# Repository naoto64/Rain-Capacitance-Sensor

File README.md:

# Rain-Capacitance-Sensor
This is the detection board for the capacitive rain sensor.

## Circuit board image

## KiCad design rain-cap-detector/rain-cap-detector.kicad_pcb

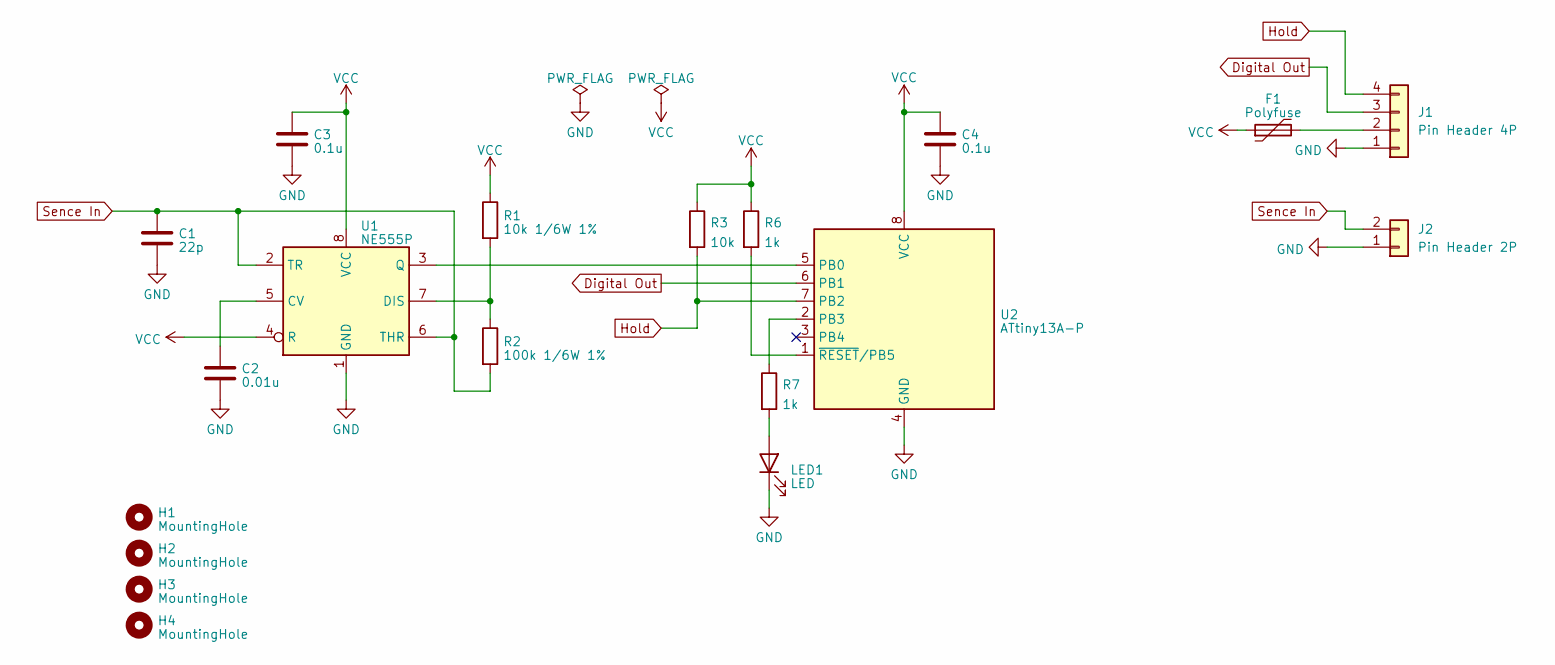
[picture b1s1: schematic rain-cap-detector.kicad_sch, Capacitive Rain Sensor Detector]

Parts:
C1: 22p; C_Disc_D3.0mm_W1.6mm_P2.50mm
C2: 0.01u; C_Disc_D3.0mm_W1.6mm_P2.50mm
C3, C4: 0.1u; C_Disc_D3.0mm_W1.6mm_P2.50mm
F1: Polyfuse; C_Disc_D4.3mm_W1.9mm_P5.00mm
H1, H2, H3, H4: MountingHole; MountingHole_2.2mm_M2
J1: Pin Header 4P; PinHeader_1x04_P2.54mm_Vertical
J2: Pin Header 2P; PinHeader_1x02_P2.54mm_Vertical
LED1: LED; LED_D3.0mm
R1: 10k 1/6W 1%; R_Axial_DIN0204_L3.6mm_D1.6mm_P5.08mm_Horizontal
R2: 100k 1/6W 1%; R_Axial_DIN0204_L3.6mm_D1.6mm_P7.62mm_Horizontal
R3: 10k; R_Axial_DIN0204_L3.6mm_D1.6mm_P5.08mm_Horizontal
R6, R7: 1k; R_Axial_DIN0204_L3.6mm_D1.6mm_P5.08mm_Horizontal
U1: NE555P; DIP-8_W7.62mm
U2: ATtiny13A-P; DIP-8_W7.62mm

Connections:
Digital Out: J1.3, U2.6 (PB1)
GND: C1.1, C2.1, C3.1, C4.2, J1.1, J2.1, LED1.1 (K), U1.1 (GND), U2.4 (GND)
Hold: J1.4, R3.2, U2.7 (PB2)
unnamed: F1.2, J1.2
unnamed: LED1.2 (A), R7.2
unnamed: C2.2, U1.5 (CV)
unnamed: R1.2, R2.1, U1.7 (DIS)
unnamed: U1.3 (Q), U2.5 (PB0)
unnamed: R7.1, U2.2 (PB3)
unnamed: R6.2, U2.1 (~RESET/PB5)
Sence In: C1.2, J2.2, R2.2, U1.2 (TR), U1.6 (THR)
VCC: C3.2, C4.1, F1.1, R1.1, R3.1, R6.1, U1.4 (R), U1.8 (VCC), U2.8 (VCC)

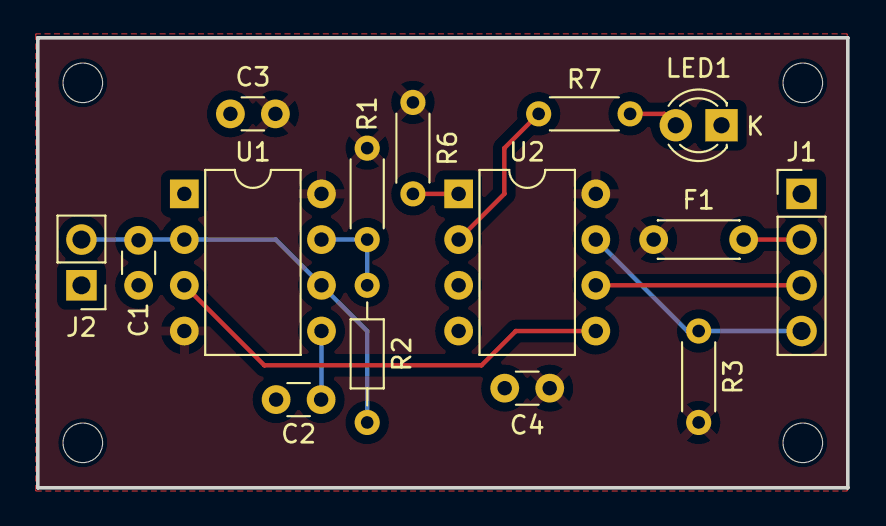
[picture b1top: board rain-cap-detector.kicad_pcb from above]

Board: 2 copper layers, 45.0 x 25.0 mm, 19 parts (0 on the bottom side), 12 nets.
